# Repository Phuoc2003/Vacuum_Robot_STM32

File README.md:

# Vacuum_Robot_STM32
Vacuum robot cleaner using STM32F1 microcontroller and others sensors.

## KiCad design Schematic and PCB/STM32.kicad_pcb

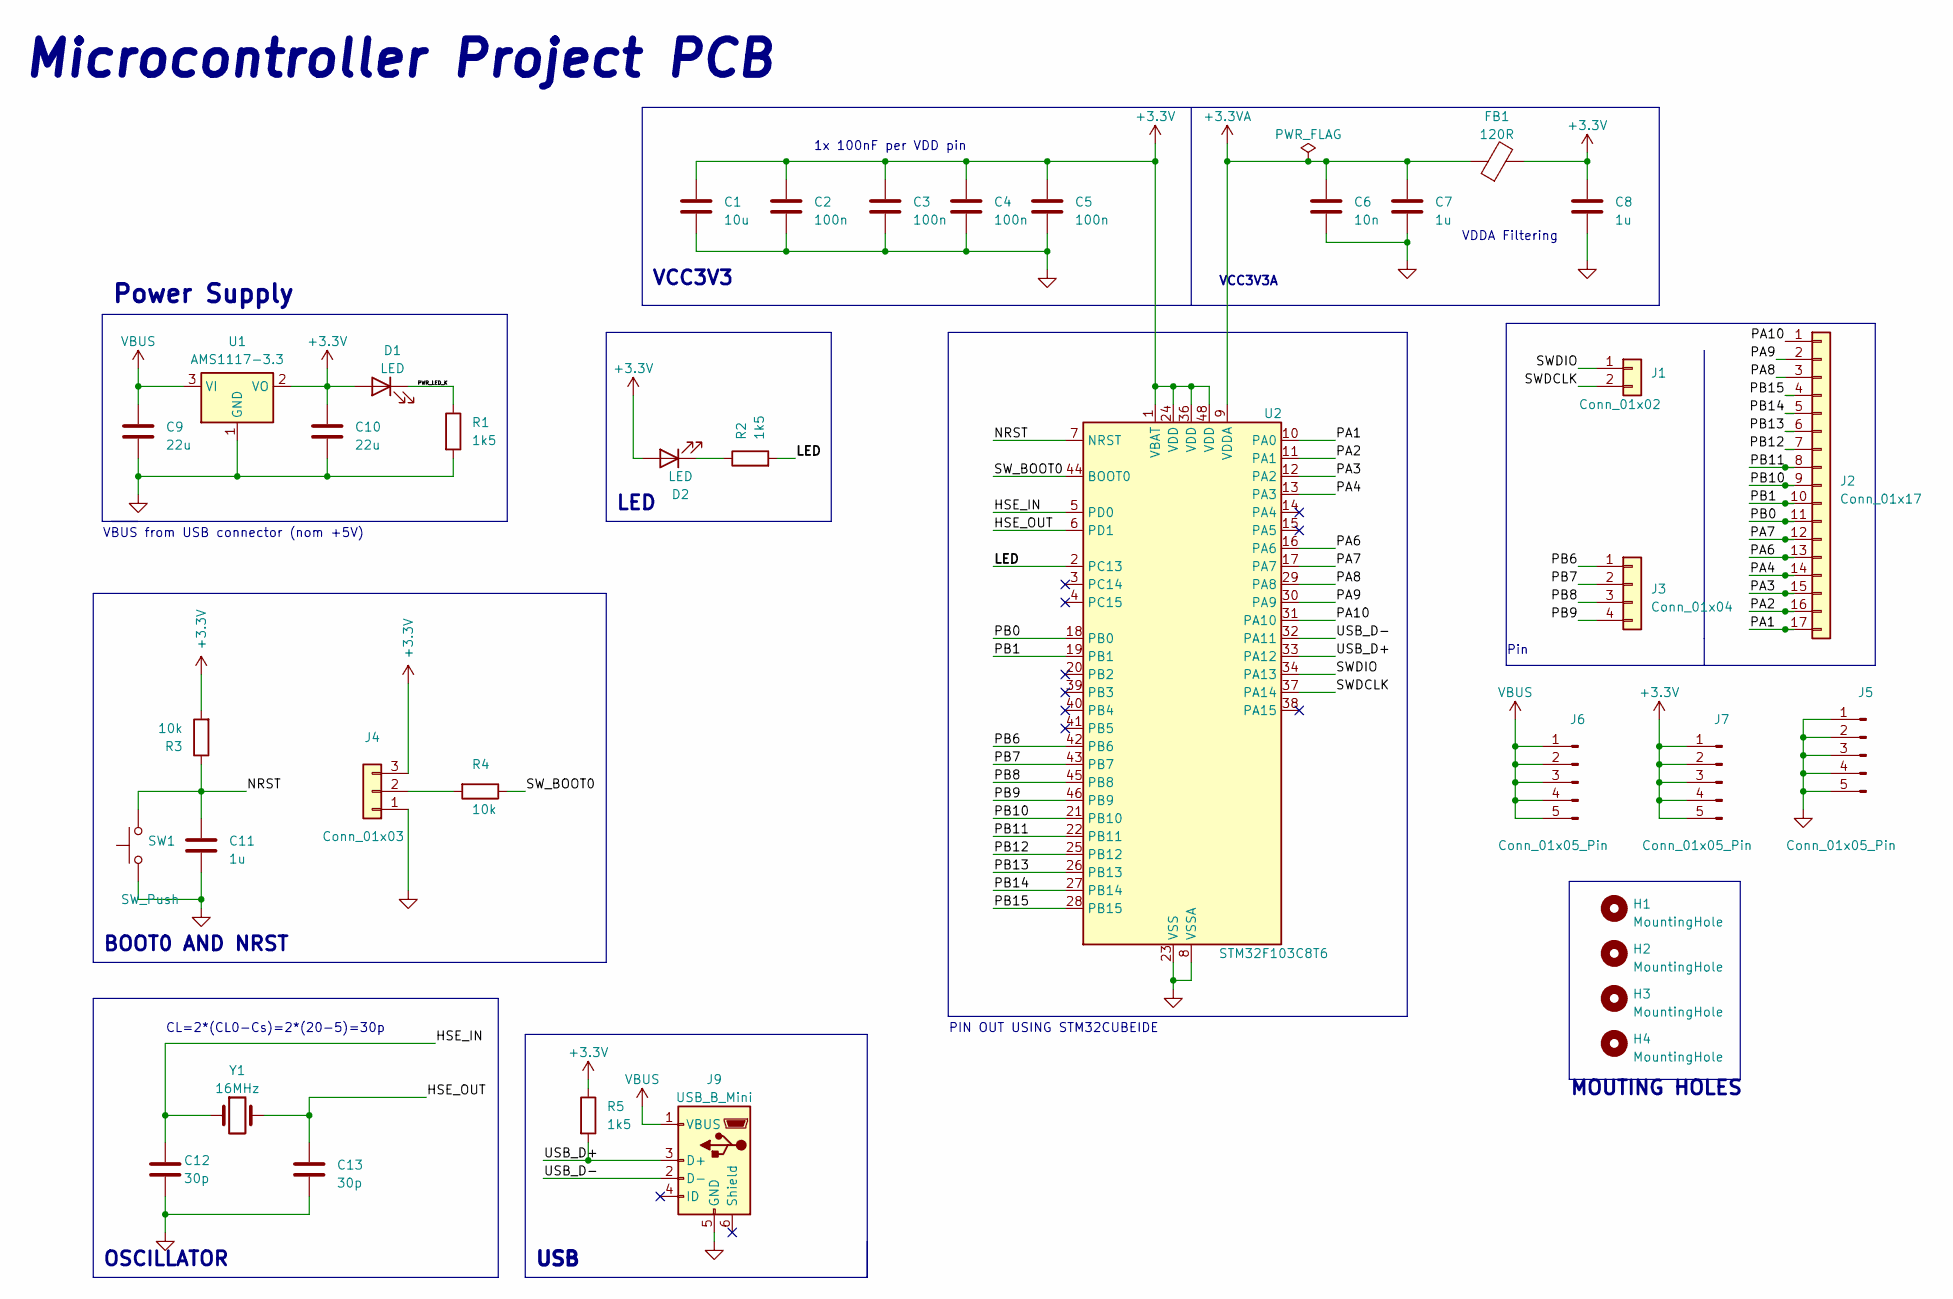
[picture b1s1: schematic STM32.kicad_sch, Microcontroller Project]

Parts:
C1: 10u; C_0805_2012Metric
C2, C3, C4, C5: 100n; C_0805_2012Metric
C6: 10n; C_0805_2012Metric
C7, C8: 1u; C_0805_2012Metric
C9, C10: 22u; C_0805_2012Metric
C11: 1u; C_0402_1005Metric
C12, C13: 30p; C_0805_2012Metric
D1, D2: LED; LED_0603_1608Metric
FB1: 120R; L_0603_1608Metric
H1, H2, H3, H4: MountingHole; MountingHole_2.2mm_M2
J1: Conn_01x02; PinHeader_1x02_P2.54mm_Vertical
J2: Conn_01x17; PinHeader_1x17_P2.54mm_Vertical
J3: Conn_01x04; PinHeader_1x04_P2.54mm_Vertical
J4: Conn_01x03; PinHeader_1x03_P2.54mm_Vertical
J5, J6, J7: Conn_01x05_Pin; PinHeader_1x05_P2.54mm_Vertical
J9: USB_B_Mini; USB_Mini-B_Lumberg_2486_01_Horizontal
R1, R2, R5: 1k5; R_0805_2012Metric
R3, R4: 10k; R_0805_2012Metric
SW1: SW_Push; SW_Push_1P1T_NO_6x6mm_H9.5mm
U1: AMS1117-3.3; SOT-223-3_TabPin2
U2: STM32F103C8T6; LQFP-48_7x7mm_P0.5mm
Y1: 16MHz; Crystal_SMD_5032-2Pin_5.0x3.2mm

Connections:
+3.3V: C1.1, C2.1, C3.1, C4.1, C5.1, C8.1, C10.1, D1.2 (A), D2.2 (A), FB1.2, J4.3, J7.1, J7.2, J7.3, J7.4, J7.5, R3.2, R5.1, U1.2 (VO), U2.1 (VBAT), U2.24 (VDD), U2.36 (VDD), U2.48 (VDD)
+3.3VA: C6.1, C7.1, FB1.1, U2.9 (VDDA)
/HSE_IN: C12.1, U2.5 (PD0), Y1.1
/HSE_OUT: C13.1, U2.6 (PD1), Y1.2
/LED: R2.2, U2.2 (PC13)
/NRST: C11.1, R3.1, SW1.2, U2.7 (NRST)
/PA1: J2.17, U2.10 (PA0)
/PA2: J2.16, U2.11 (PA1)
/PA3: J2.15, U2.12 (PA2)
/PA4: J2.14, U2.13 (PA3)
/PA6: J2.13, U2.16 (PA6)
/PA7: J2.12, U2.17 (PA7)
/PA8: J2.3, U2.29 (PA8)
/PA9: J2.2, U2.30 (PA9)
/PA10: J2.1, U2.31 (PA10)
/PB0: J2.11, U2.18 (PB0)
/PB1: J2.10, U2.19 (PB1)
/PB6: J3.1, U2.42 (PB6)
/PB7: J3.2, U2.43 (PB7)
/PB8: J3.3, U2.45 (PB8)
/PB9: J3.4, U2.46 (PB9)
/PB10: J2.9, U2.21 (PB10)
/PB11: J2.8, U2.22 (PB11)
/PB12: J2.7, U2.25 (PB12)
/PB13: J2.6, U2.26 (PB13)
/PB14: J2.5, U2.27 (PB14)
/PB15: J2.4, U2.28 (PB15)
/PWR_LED_K: D1.1 (K), R1.1
/SWDCLK: J1.2, U2.37 (PA14)
/SWDIO: J1.1, U2.34 (PA13)
/SW_BOOT0: R4.1, U2.44 (BOOT0)
/USB_D+: J9.3 (D+), R5.2, U2.33 (PA12)
/USB_D-: J9.2 (D-), U2.32 (PA11)
GND: C1.2, C2.2, C3.2, C4.2, C5.2, C6.2, C7.2, C8.2, C9.2, C10.2, C11.2, C12.2, C13.2, J4.1, J5.1, J5.2, J5.3, J5.4, J5.5, J9.5 (GND), R1.2, SW1.1, U1.1 (GND), U2.8 (VSSA), U2.23 (VSS), U2.35 (VSS), U2.47 (VSS)
unnamed: D2.1 (K), R2.1
unnamed: J4.2, R4.2
VBUS: C9.1, J6.1, J6.2, J6.3, J6.4, J6.5, J9.1 (VBUS), U1.3 (VI)

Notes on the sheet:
1x 100nF per VDD pin
VCC3V3
MOUTING HOLES
LED
VCC3V3A
PIN OUT USING STM32CUBEIDE
Pin
Power Supply
VBUS from USB connector (nom +5V)
OSCILLATOR
VDDA Filtering
CL=2*(CL0-Cs)=2*(20-5)=30p
Microcontroller Project PCB
BOOT0 AND NRST
USB

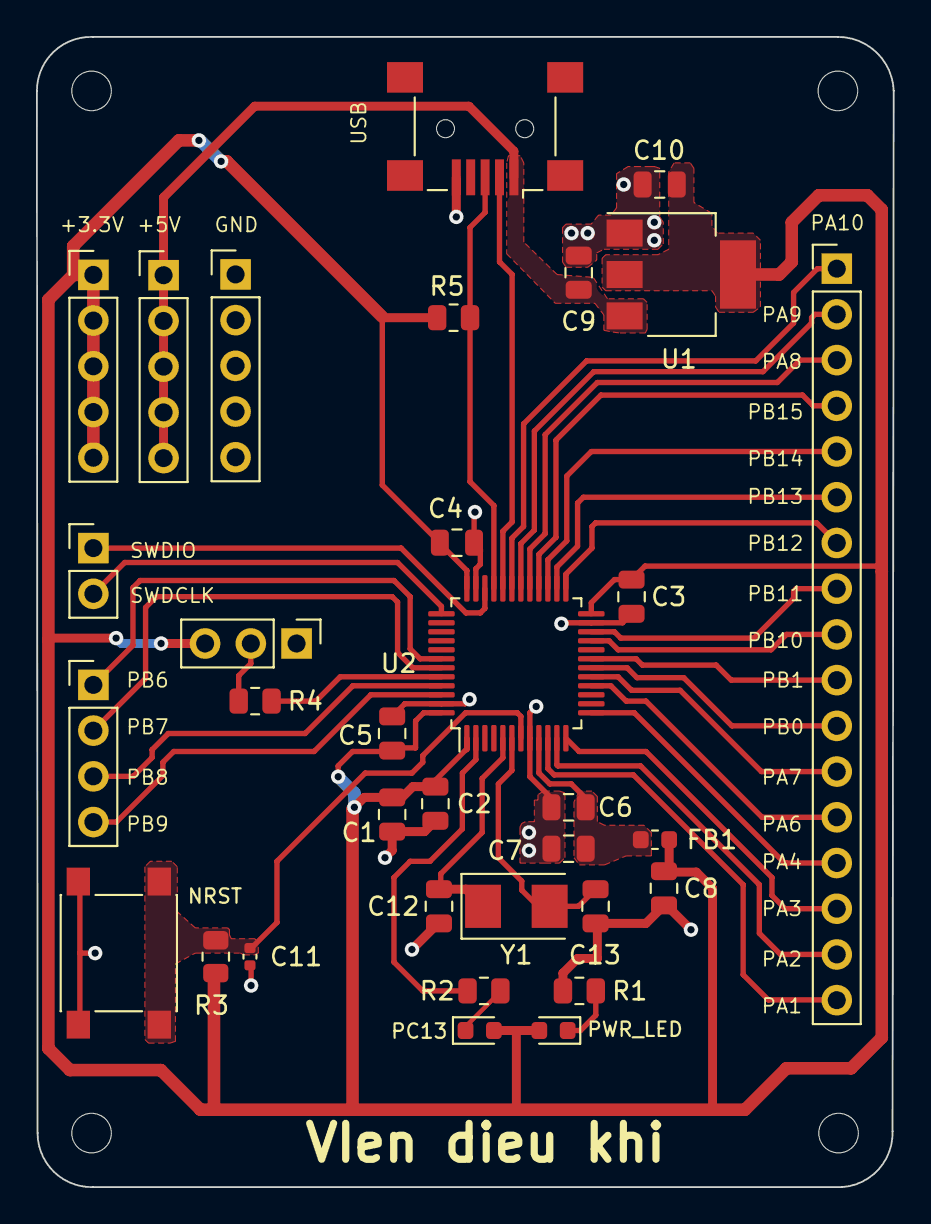
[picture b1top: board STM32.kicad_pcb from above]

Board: 2 copper layers, 47.6 x 63.9 mm, 37 parts (0 on the bottom side), 37 nets.

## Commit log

2023-06-26 Add Core, Drivers and ECUAL folder
2023-07-07 Update Robot algorithm to run smoother.
2023-07-07 Add schematic and PCB file.
2023-07-07 Change file name and function name.
2023-07-07 Change function name.
